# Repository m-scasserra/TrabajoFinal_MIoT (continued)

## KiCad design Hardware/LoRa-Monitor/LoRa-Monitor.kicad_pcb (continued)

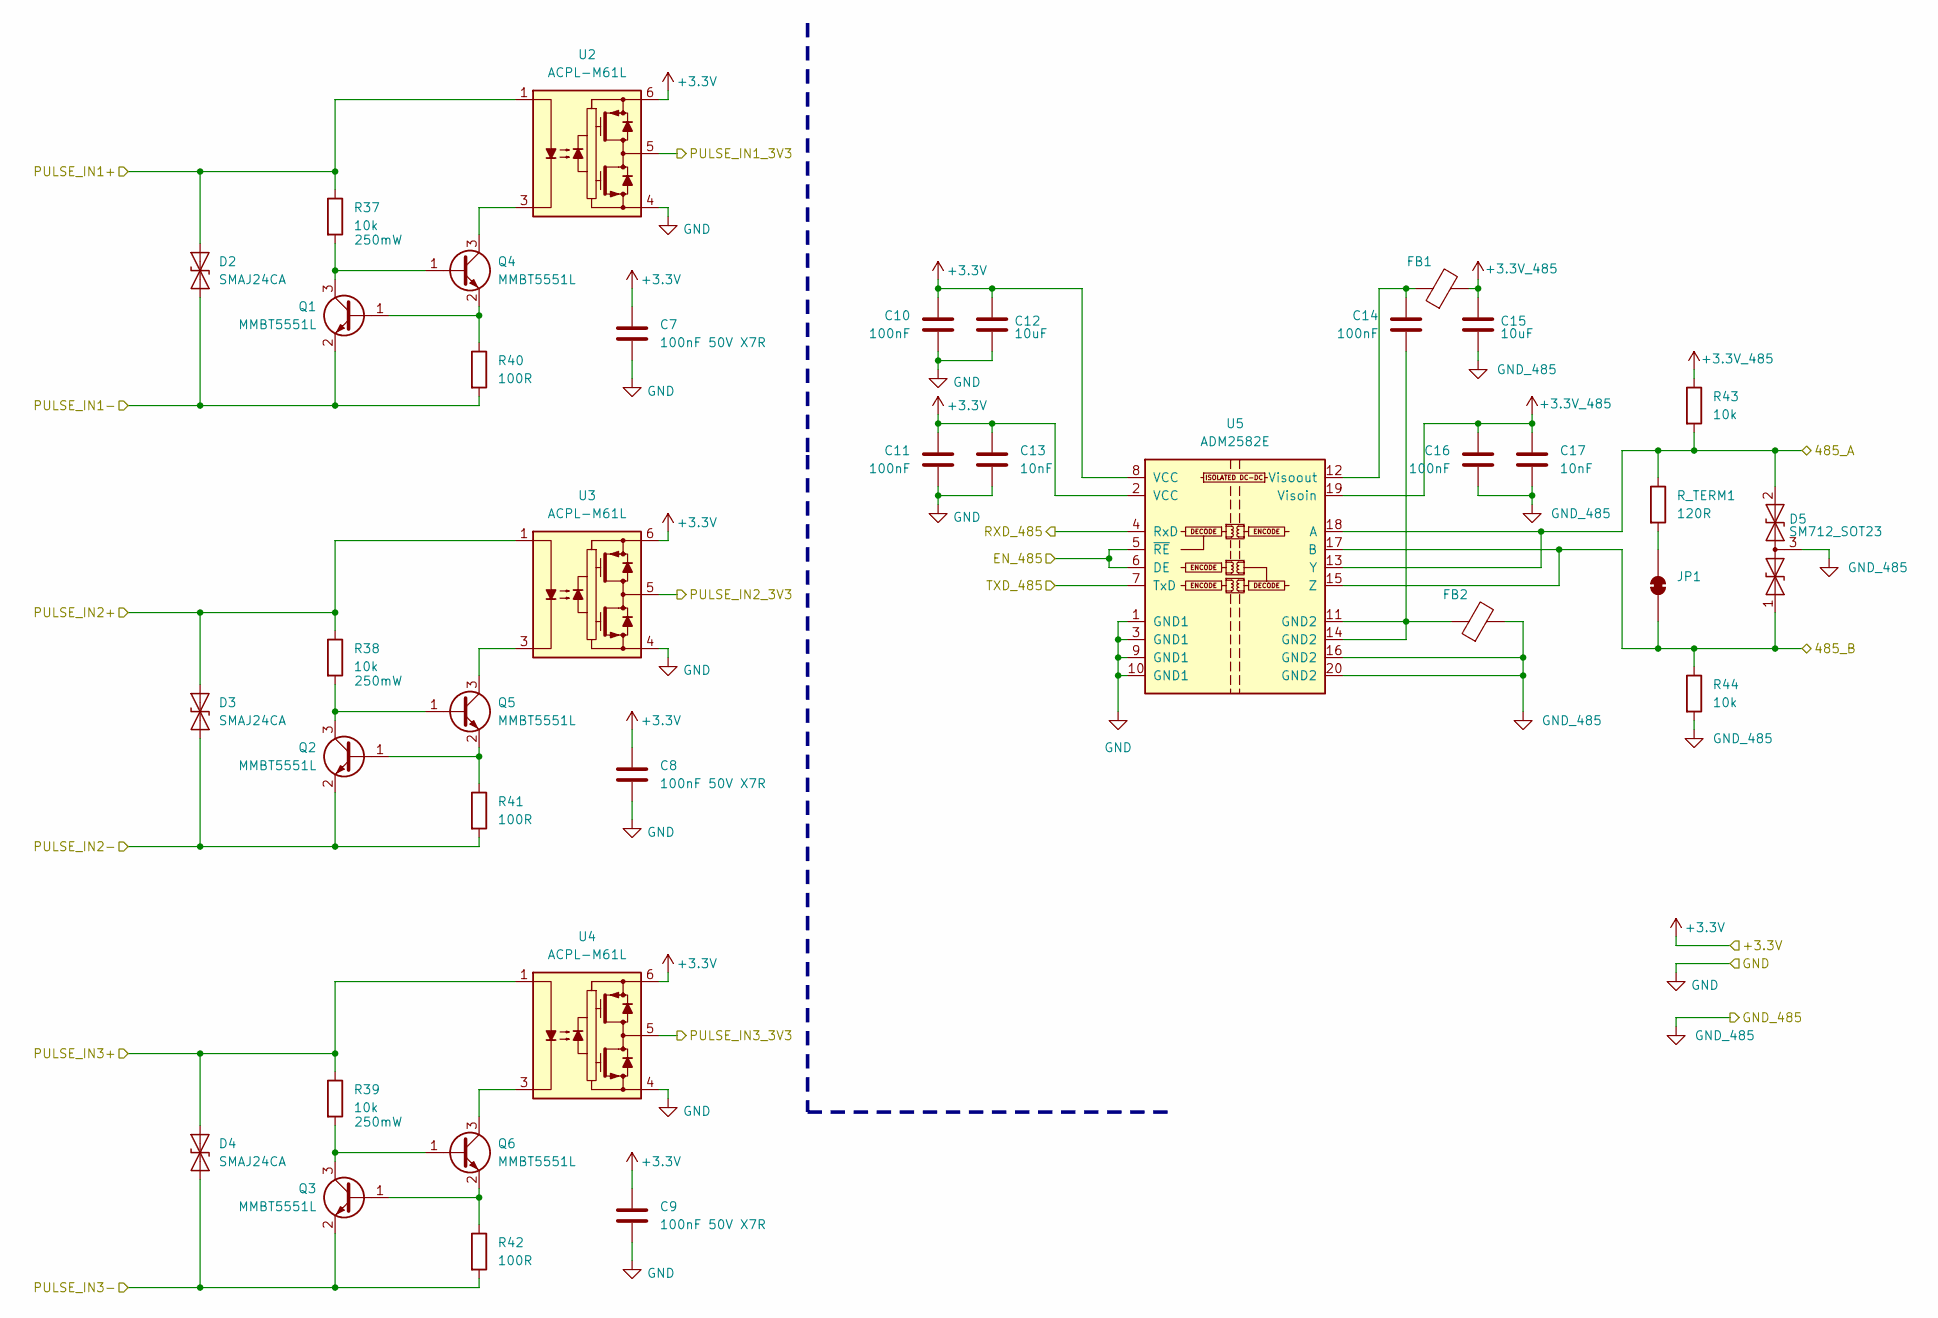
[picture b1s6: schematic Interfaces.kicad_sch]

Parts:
C7, C8, C9: 100nF 50V X7R; C_0805_2012Metric; LCSC Part # C49678
C10, C11, C14, C16: 100nF; C_0805_2012Metric; LCSC Part # C49678
C12, C15: 10uF; C_0805_2012Metric; LCSC Part # C15850
C13, C17: 10nF; C_0805_2012Metric; LCSC Part # C1710
D2, D3, D4: SMAJ24CA; D_SMA; LCSC Part # C113963
D5: SM712_SOT23; SOT-23; LCSC Part # C521963
FB1, FB2: FerriteBead; L_0603_1608Metric; LCSC Part # C2942905
JP1: SolderJumper_2_Bridged; SolderJumper-2_P1.3mm_Bridged_RoundedPad1.0x1.5mm
Q1, Q2, Q3, Q4, Q5, Q6: MMBT5551L; SOT-23; LCSC Part # C2145
R37, R38, R39: 10k; R_1206_3216Metric; LCSC Part # C17902
R40, R41, R42: 100R; R_0805_2012Metric; LCSC Part # C17408
R43, R44: 10k; R_0805_2012Metric; LCSC Part # C17414
R_TERM1: 120R; R_0805_2012Metric; LCSC Part # C17437
U2, U3, U4: ACPL-M61L; SO-5_4.39x3.84mm_P1.27mm; LCSC Part # C691956
U5: ADM2582E; SOIC-20W_7.5x12.8mm_P1.27mm; LCSC Part # C39494

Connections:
+3.3V: C7.1, C8.1, C9.1, C10.1, C11.1, C12.1, C13.1, U2.6 (VCC), U3.6 (VCC), U4.6 (VCC), U5.2 (VCC), U5.8 (VCC); also elsewhere on the board
+3.3V_485: C15.1, C16.1, C17.1, FB1.2, R43.1, U5.19 (Visoin)
/Connectors/485_A: D5.2 (A2), R43.2, R_TERM1.1, U5.13 (Y), U5.18 (A); also elsewhere on the board
/Connectors/485_B: D5.1 (A1), JP1.1 (A), R44.1, U5.15 (Z), U5.17 (B); also elsewhere on the board
/Connectors/PULSE_IN1+: D2.2 (A2), R37.1, U2.1 (A); also elsewhere on the board
/Connectors/PULSE_IN1-: D2.1 (A1), Q1.2 (E), R40.2; also elsewhere on the board
/Connectors/PULSE_IN2+: D3.2 (A2), R38.1, U3.1 (A); also elsewhere on the board
/Connectors/PULSE_IN2-: D3.1 (A1), Q2.2 (E), R41.2; also elsewhere on the board
/Connectors/PULSE_IN3+: D4.2 (A2), R39.1, U4.1 (A); also elsewhere on the board
/Connectors/PULSE_IN3-: D4.1 (A1), Q3.2 (E), R42.2; also elsewhere on the board
/Energy Meter Interface Module/EN_485: U5.5 (~RE), U5.6 (DE); also elsewhere on the board
/Energy Meter Interface Module/PULSE_IN1_3V3: U2.5 (VO); also elsewhere on the board
/Energy Meter Interface Module/PULSE_IN2_3V3: U3.5 (VO); also elsewhere on the board
/Energy Meter Interface Module/PULSE_IN3_3V3: U4.5 (VO); also elsewhere on the board
/Energy Meter Interface Module/RXD_485: U5.4 (RxD); also elsewhere on the board
/Energy Meter Interface Module/TXD_485: U5.7 (TxD); also elsewhere on the board
GND: C7.2, C8.2, C9.2, C10.2, C11.2, C12.2, C13.2, U2.4 (VEE), U3.4 (VEE), U4.4 (VEE), U5.1 (GND1), U5.3 (GND1), U5.9 (GND1), U5.10 (GND1); also elsewhere on the board
GND_485: C15.2, C16.2, C17.2, D5.3 (common), FB2.2, R44.2, U5.16 (GND2), U5.20 (GND2); also elsewhere on the board
unnamed: C14.2, FB2.1, U5.11 (GND2), U5.14 (GND2)
unnamed: JP1.2 (B), R_TERM1.2
unnamed: Q1.1 (B), Q4.2 (E), R40.1
unnamed: Q1.3 (C), Q4.1 (B), R37.2
unnamed: Q2.1 (B), Q5.2 (E), R41.1
unnamed: Q2.3 (C), Q5.1 (B), R38.2
unnamed: Q3.1 (B), Q6.2 (E), R42.1
unnamed: Q3.3 (C), Q6.1 (B), R39.2
unnamed: Q4.3 (C), U2.3 (C)
unnamed: Q5.3 (C), U3.3 (C)
unnamed: Q6.3 (C), U4.3 (C)
unnamed: C14.1, FB1.1, U5.12 (Visoout)

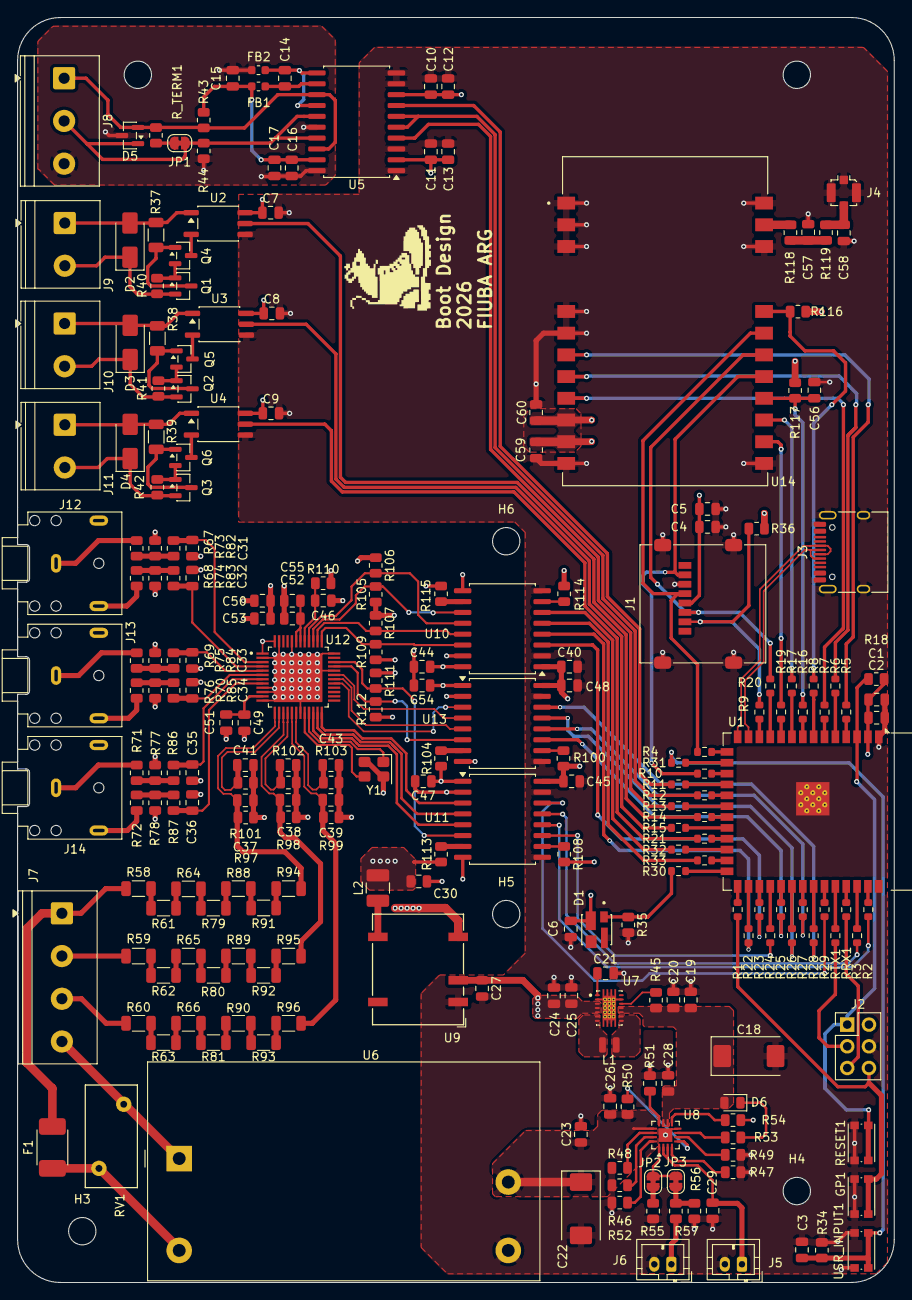
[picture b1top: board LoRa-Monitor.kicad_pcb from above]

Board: 4 copper layers, 102.6 x 148.0 mm, 241 parts (0 on the bottom side), 191 nets.

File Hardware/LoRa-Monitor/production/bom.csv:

Designator,Footprint,Quantity,Value,LCSC Part #
"C1, C12, C15, C30, C4, C49, C52, C57, C58, C59",0805,10,10uF,C15850
"C10, C11, C14, C16, C3",0805,5,100nF,C49678
"C13, C17",0805,2,10nF,C1710
"C18, C22",CP_EIA-7343-31_Kemet-D,2,100uF 16V,C7223
"C19, C24, C25",0805,3,22uF,C45783
"C2, C20, C21, C23, C40, C44, C45, C46, C47, C48, C5, C50, C51, C53, C54, C55, C56, C6, C60, C7, C8, C9",0805,22,100nF 50V X7R,C49678
"C26, C27, C29",0805,3,1uF 50V X7R,C28323
C28,0805,1,4.7uF 25V X7R,C1779
"C31, C32, C33, C34, C35, C36, C37, C38, C39, C41, C42, C43",0805,12,18nF,C1723
D1,LED_SK6812MINI-012,1,SK6812MINI-012,C2886570
"D2, D3, D4",D_SMA,3,SMAJ24CA,C113963
D5,SOT-23,1,SM712_SOT23,C521963
D6,0805,1,LED,C84256
F1,2410,1,MF2410F2.000TM,C83797
"FB1, FB2",0603,2,FerriteBead,C2942905
"GP1, RESET1, USR_INPUT1",SW_Push_1P1T_NO_CK_KMR2,3,SW_Push,C72443
J1,microSD_HC_Molex_47219-2001,1,Micro_SD_Card,C164170
"J10, J11, J9","TerminalBlock_Phoenix_PT-1,5-2-5.0-H_1x02_P5.00mm_Horizontal",3,Screw_Terminal_01x02,C3819953
"J12, J13, J14",Jack_3.5mm_CUI_SJ1-3523N_Horizontal,3,AudioJack3,C20182914
J2,PinHeader_2x03_P2.54mm_Vertical,1,Conn_02x03_Odd_Even,
J3,USB_C_Receptacle_HRO_TYPE-C-31-M-12,1,USB_C_Receptacle_USB2.0_16P,C165948
J4,U.FL_Molex_MCRF_73412-0110_Vertical,1,Conn_Coaxial,C434806
"J5, J6",JST_PH_B2B-PH-K_1x02_P2.00mm_Vertical,2,Conn_01x02_Pin,C131337
J7,"TerminalBlock_Phoenix_PT-1,5-4-5.0-H_1x04_P5.00mm_Horizontal",1,Screw_Terminal_01x04,C3817931
J8,"TerminalBlock_Phoenix_PT-1,5-3-5.0-H_1x03_P5.00mm_Horizontal",1,Screw_Terminal_01x03,C3816891
L1,0806,1,1uH,C161082
L2,1210,1,15uH,C250232
"Q1, Q2, Q3, Q4, Q5, Q6",SOT-23,6,MMBT5551L,C2145
"R1, R10, R11, R12, R13, R14, R15, R16, R17, R19, R2, R20, R21, R22, R23, R24, R25, R26, R27, R28, R29, R3, R30, R31, R32, R33, R4, R5, R6, R7, R8, R9, RRX1, RTX1",0603,34,0R,C21189
"R100, R104, R105, R106, R107, R108, R109, R110, R111, R112, R113, R114, R115, R116, R117, R118, R119, R18, R34, R35, R36, R43, R44, R45, R46, R47, R49, R50, R55",0805,29,10k,C17414
"R101, R102, R103, R82, R83, R84, R85, R86, R87, R97, R98, R99",0805,12,1k,C17513
"R37, R38, R39",1206,3,10k,C17902
"R40, R41, R42",0805,3,100R,C17408
R48,0805,1,46.4k,C483162
"R51, R53, R54, R56",0805,4,1.1k,C185294
R52,0805,1,590R,C55566
R57,0805,1,140k,C17460
"R58, R59, R60, R61, R62, R63, R64, R65, R66, R79, R80, R81, R88, R89, R90, R91, R92, R93, R94, R95, R96",1206,21,240k,C18001
"R67, R68, R69, R70, R71, R72",0805,6,0R,C17477
"R73, R74, R75, R76, R77, R78",0805,6,2.4R,C17528
RV1,RV_Disc_D12mm_W6.1mm_P7.5mm,1,10D561K,C2656193
R_TERM1,0805,1,120R,C17437
U1,ESP32-S3-WROOM-1,1,ESP32-S3-WROOM-1,C2913205
"U10, U11, U13",SOIC-16W_7.5x10.3mm_P1.27mm,3,ADuM1401xRW,C91762
U12,QFP50P900X900X120-48N,1,ATM90E32AS-AU-R,C177153
U14,XCVR_E22-900M30S,1,E22-900M30S,C411294
"U2, U3, U4",SO-5_4.39x3.84mm_P1.27mm,3,ACPL-M61L,C691956
U5,SOIC-20W_7.5x12.8mm_P1.27mm,1,ADM2582E,C39494
U6,Converter_ACDC_MeanWell_IRM-05-xx_THT,1,IRM-05-5,C48603696
U7,IC_TPS63021DSJR,1,TPS63021DSJR,C202140
U8,VQFN-16-1EP_3x3mm_P0.5mm_EP1.6x1.6mm,1,BQ24072RGT,C140288
U9,Converter_DCDC_Murata_NXExSxxxxMC_SMD,1,NXE1S0303MC,C20606969
Y1,Crystal_SMD_3225-4Pin_3.2x2.5mm,1,16.384MHz,C13739

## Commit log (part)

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2026-06-03 Add LED driver implementation with CMake configuration and interface
2026-06-03 Add VSCode configuration files for ESP-IDF development
2026-06-03 Add initial project files including CMakeLists, Makefile, .gitignore, and documentation
2026-06-03 Add test application files including CMake configuration, test cases, and pytest integration for LED functionality
2026-06-03 Add .gitignore to exclude greeting component files from version control
2026-06-03 Add main application file and CMake configuration for LED control
2026-06-03 Add Dockerfile and devcontainer configuration for ESP-IDF development
2026-06-03 Add .gitignore to exclude .NET build output and VS Code files
2026-06-03 Add initial .NET Core Console application files including project configuration, launch settings, and build tasks
2026-06-08 Added hardware files and updated gitihone
2026-06-08 Deleted lck files
2026-06-08 Fixed Power and Ground on the Interface nodes
2026-06-09 Added PSU
2026-06-09 Added more PSU components.
2026-06-10 Finished PSU module, started Energy meter
2026-06-10 Finished Energy Meter Module, started LoRa Module and MCU.
2026-06-10 Finished MCU and Lora modules. Finished Connectors sheet
2026-06-11 Finished schematic, started with PCB design
2026-06-11 Started routing.
2026-06-12 Finished the first component disposition
